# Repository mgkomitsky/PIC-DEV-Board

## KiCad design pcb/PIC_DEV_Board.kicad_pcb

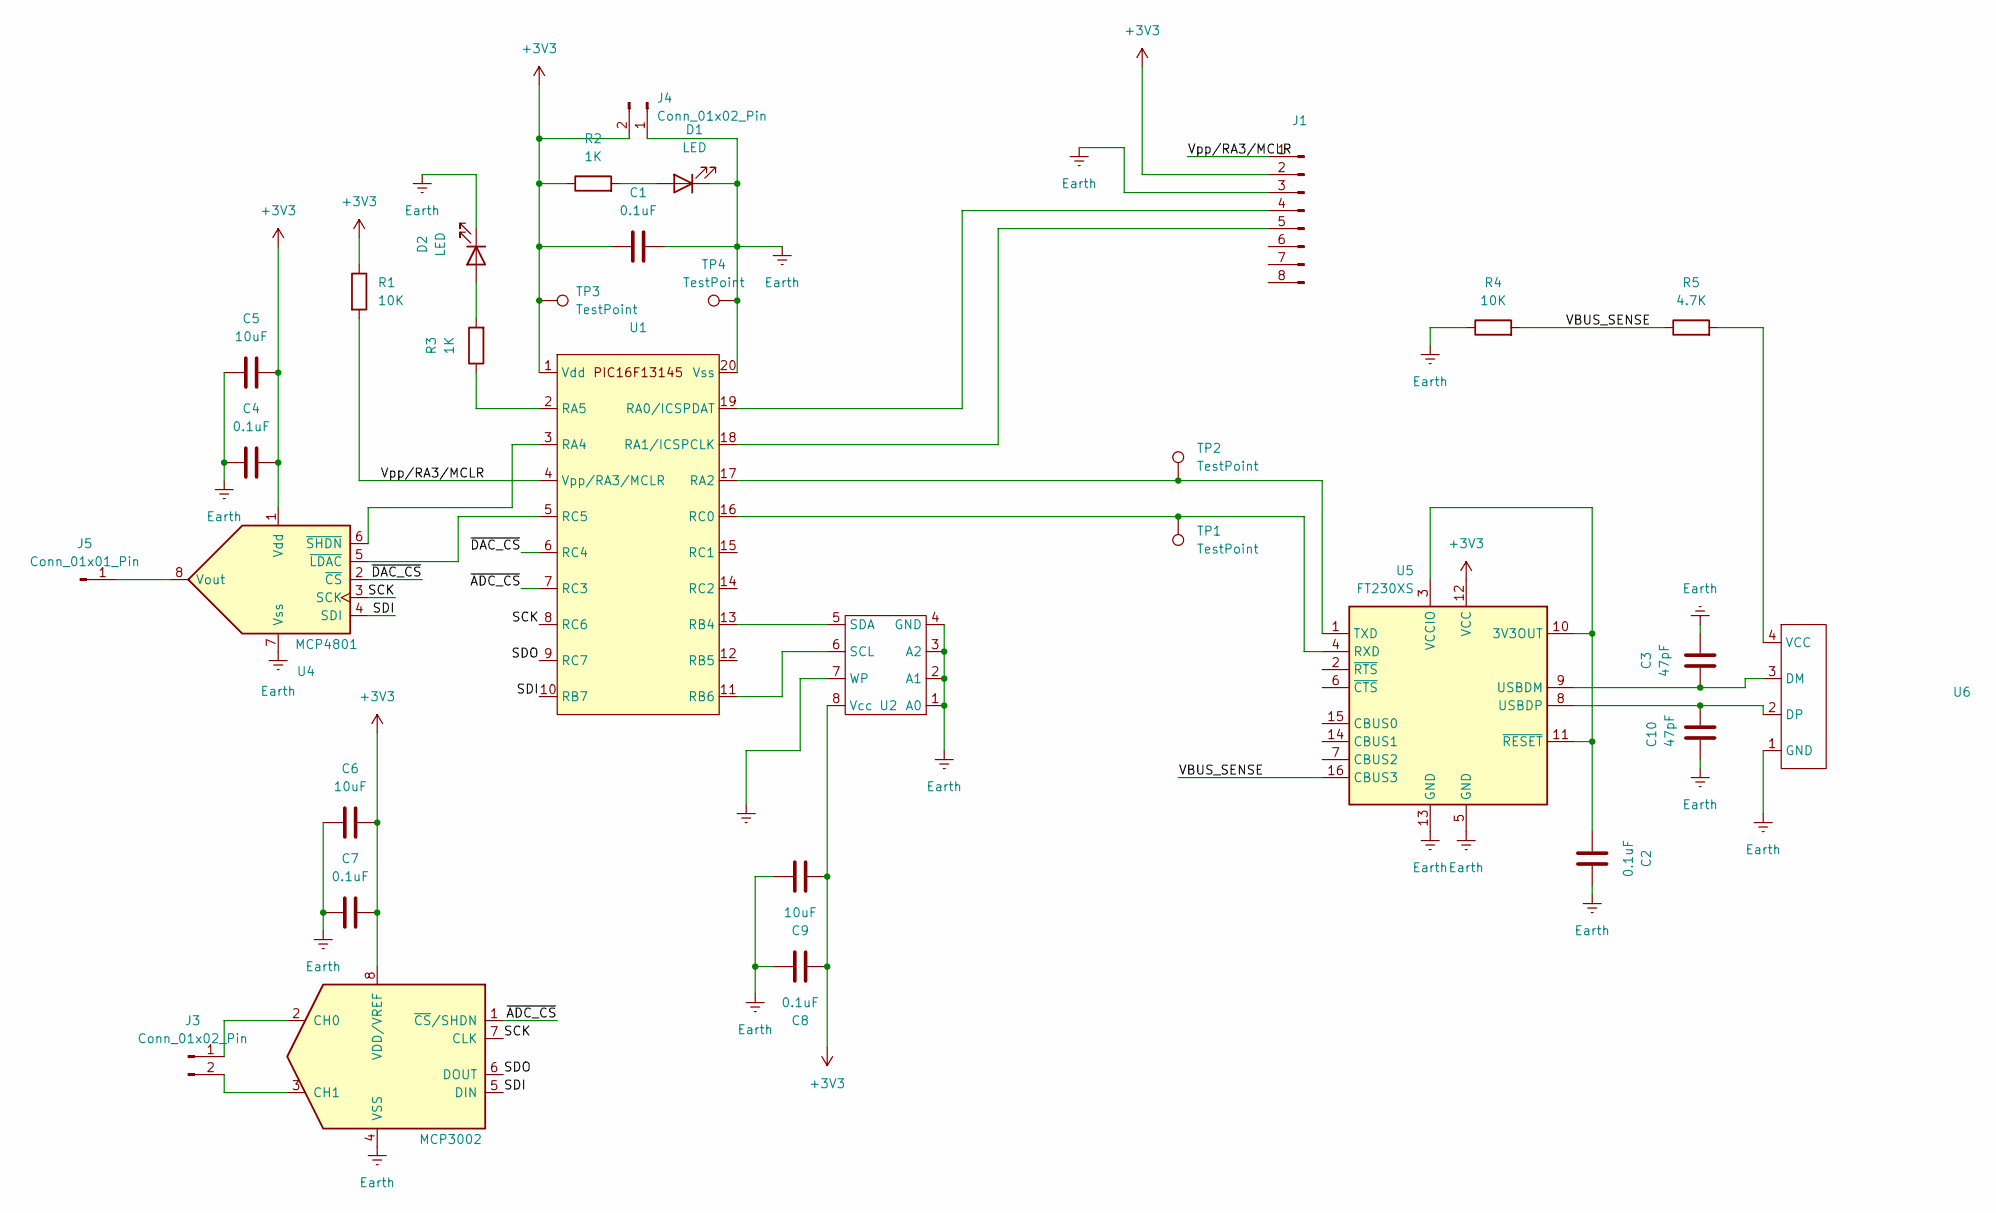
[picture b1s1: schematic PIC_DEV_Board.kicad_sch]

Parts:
C1, C2, C4, C7, C8: 0.1uF; C_0805_2012Metric
C3, C10: 47pF; C_0805_2012Metric
C5, C6, C9: 10uF; C_0805_2012Metric
D1, D2: LED; LED_0805_2012Metric
J1: Conn_01x08_Pin; PinHeader_1x08_P2.54mm_Vertical
J3, J4: Conn_01x02_Pin; PinHeader_1x02_P2.54mm_Vertical
J5: Conn_01x01_Pin; PinHeader_1x01_P2.54mm_Vertical
R1, R4: 10K; R_0805_2012Metric
R2, R3: 1K; R_0805_2012Metric
R5: 4.7K; R_0805_2012Metric
TP1, TP2, TP3, TP4: TestPoint; TestPoint_Pad_1.5x1.5mm
U1: SOIC-20W_7.5x12.8mm_P1.27mm
U2: SOIC-8_3.9x4.9mm_P1.27mm
U3: MCP3002; SOIC-8_3.9x4.9mm_P1.27mm
U4: MCP4801; SOIC-8_3.9x4.9mm_P1.27mm
U5: FT230XS; SSOP-16_3.9x4.9mm_P0.635mm
U6: USB-A1HSB6

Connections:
+3V3: C1.2, C4.1, C5.1, C6.1, C7.1, C8.1, C9.1, J1.2, J4.2, R1.1, R2.1, TP3.1, U1.1 (Vdd), U2.8 (Vcc), U3.8 (VDD/VREF), U4.1 (Vdd), U5.12 (VCC)
/SCK: U1.8 (RC6), U3.7 (CLK), U4.3 (SCK)
/SDI: U1.10 (RB7), U3.5 (DIN), U4.4 (SDI)
/SDO: U1.9 (RC7), U3.6 (DOUT)
/VBUS_SENSE: R4.2, R5.1, U5.16 (CBUS3)
/~ADC_CS: U1.7 (RC3), U3.1 (~CS/SHDN)
/~DAC_CS: U1.6 (RC4), U4.2 (~CS)
Earth: C1.1, C2.2, C3.2, C4.2, C5.2, C6.2, C7.2, C8.2, C9.2, C10.2, D1.1 (K), D2.1 (K), J1.3, J4.1, R4.1, TP4.1, U1.20 (Vss), U2.1 (A0), U2.2 (A1), U2.3 (A2), U2.4 (GND), U2.7 (WP), U3.4 (VSS), U4.7 (Vss), U5.5 (GND), U5.13 (GND), U6.1 (GND)
unnamed: D1.2 (A), R2.2
unnamed: D2.2 (A), R3.2
unnamed: J1.4, U1.19 (RA0/ICSPDAT)
unnamed: J1.5, U1.18 (RA1/ICSPCLK)
unnamed: J3.1, U3.2 (CH0)
unnamed: J3.2, U3.3 (CH1)
unnamed: J5.1, U4.8 (Vout)
unnamed: TP2.1, U1.17 (RA2), U5.1 (TXD)
unnamed: U1.3 (RA4), U4.6 (~SHDN)
unnamed: R3.1, U1.2 (RA5)
unnamed: U1.13 (RB4), U2.5 (SDA)
unnamed: U1.11 (RB6), U2.6 (SCL)
unnamed: TP1.1, U1.16 (RC0), U5.4 (RXD)
unnamed: U1.5 (RC5), U4.5 (~LDAC)
unnamed: C2.1, U5.3 (VCCIO), U5.10 (3V3OUT), U5.11 (~RESET)
unnamed: C3.1, U5.9 (USBDM), U6.3 (DM)
unnamed: C10.1, U5.8 (USBDP), U6.2 (DP)
unnamed: R5.2, U6.4 (VCC)

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
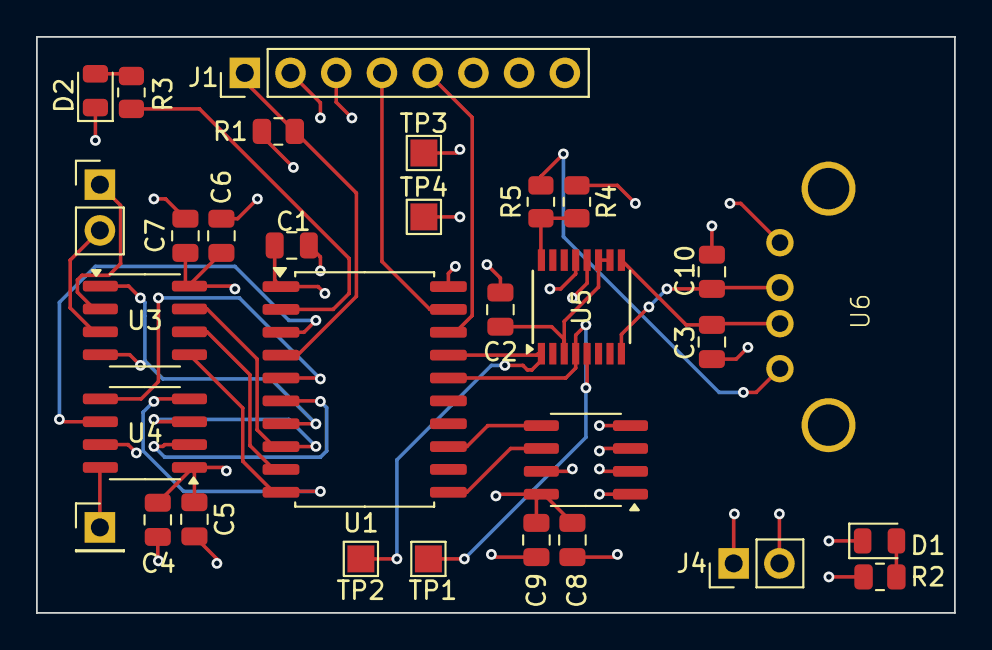
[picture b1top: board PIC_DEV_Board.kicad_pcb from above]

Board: 4 copper layers, 51.0 x 32.0 mm, 31 parts (0 on the bottom side), 27 nets.

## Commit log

2024-03-30 trace updates
2024-03-31 silkscreen
2024-04-01 higher functionality board
2024-04-02 size reduction
2024-04-02 layout changes
2024-04-02 layout/schematic changes
2024-04-02 layout/via changes
2024-04-05 Rev02_GBR
2024-04-05 Rev02 final
